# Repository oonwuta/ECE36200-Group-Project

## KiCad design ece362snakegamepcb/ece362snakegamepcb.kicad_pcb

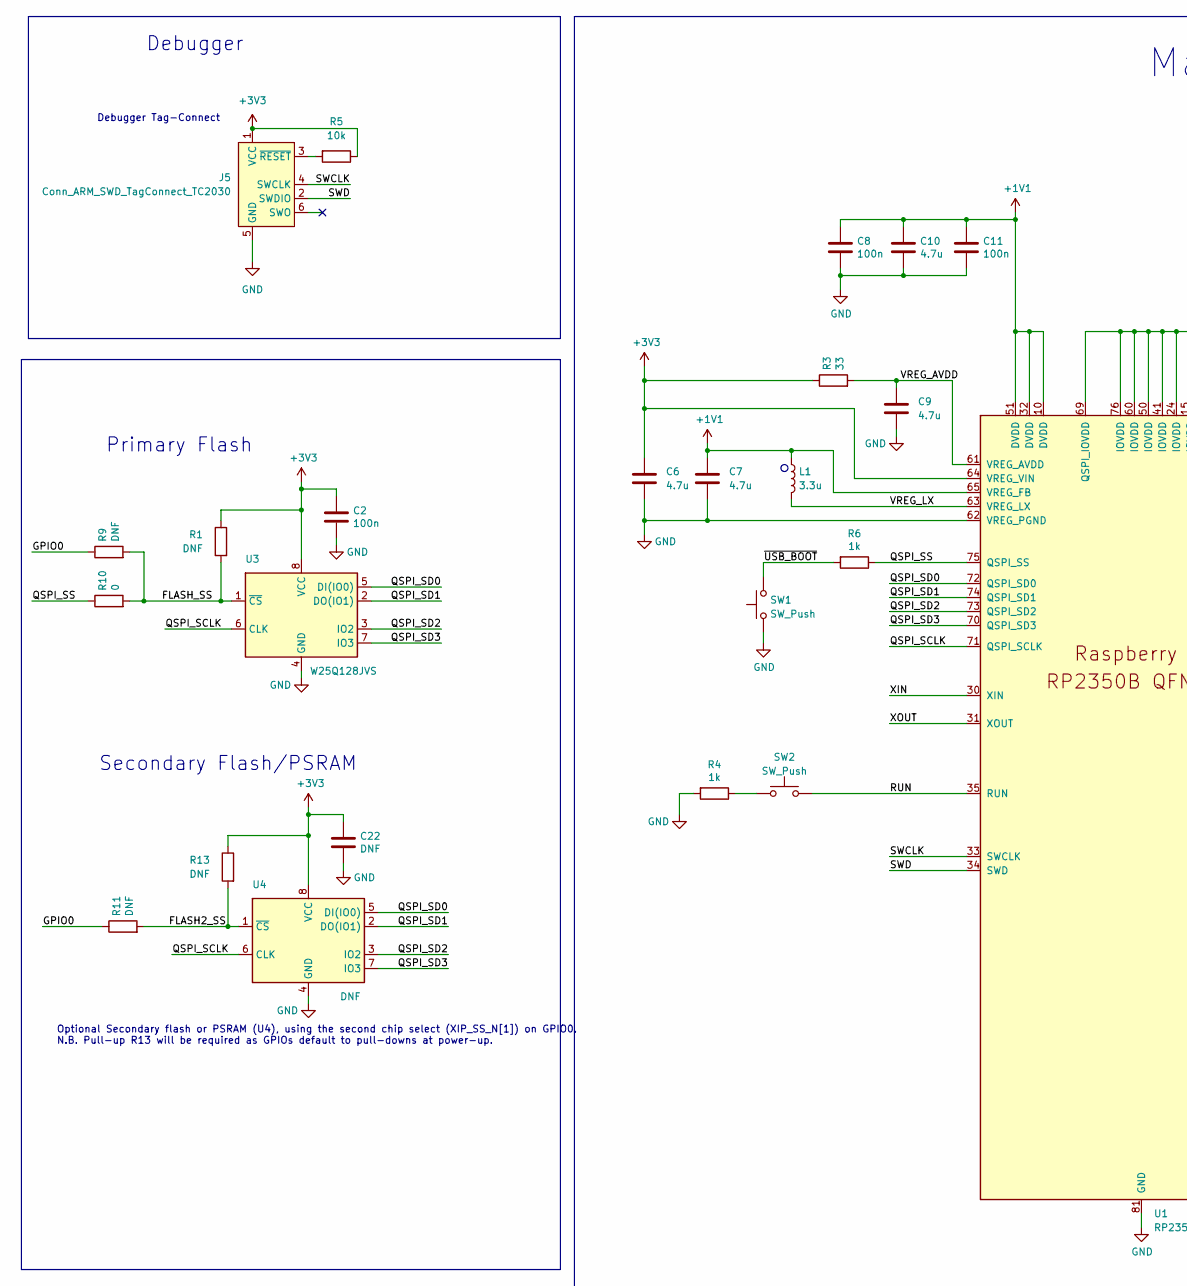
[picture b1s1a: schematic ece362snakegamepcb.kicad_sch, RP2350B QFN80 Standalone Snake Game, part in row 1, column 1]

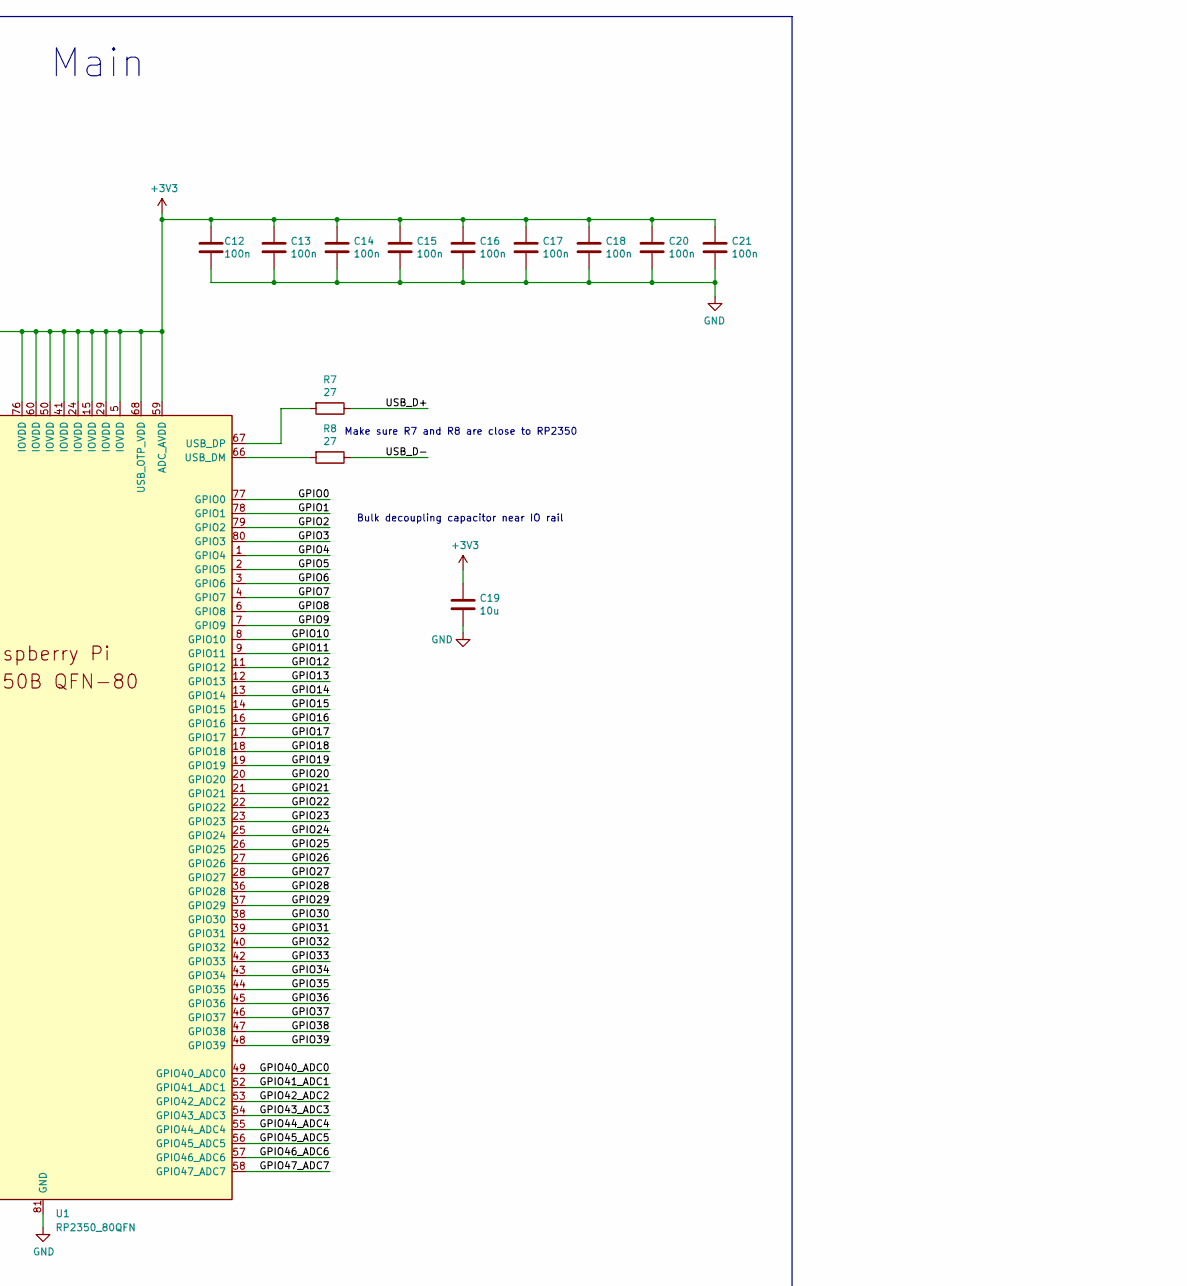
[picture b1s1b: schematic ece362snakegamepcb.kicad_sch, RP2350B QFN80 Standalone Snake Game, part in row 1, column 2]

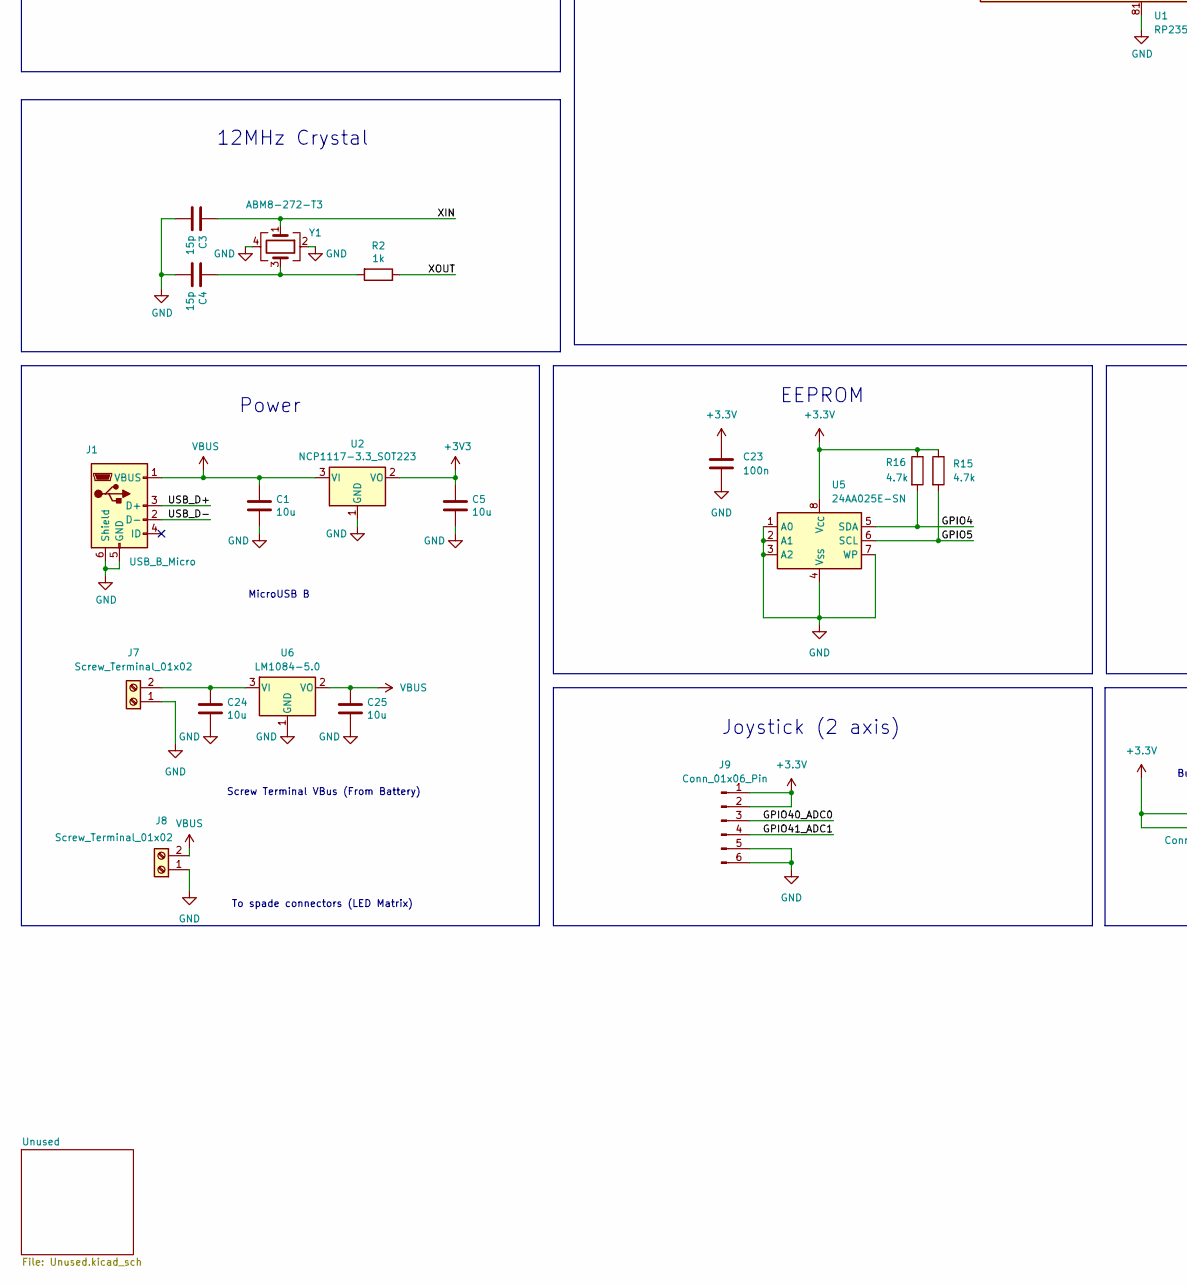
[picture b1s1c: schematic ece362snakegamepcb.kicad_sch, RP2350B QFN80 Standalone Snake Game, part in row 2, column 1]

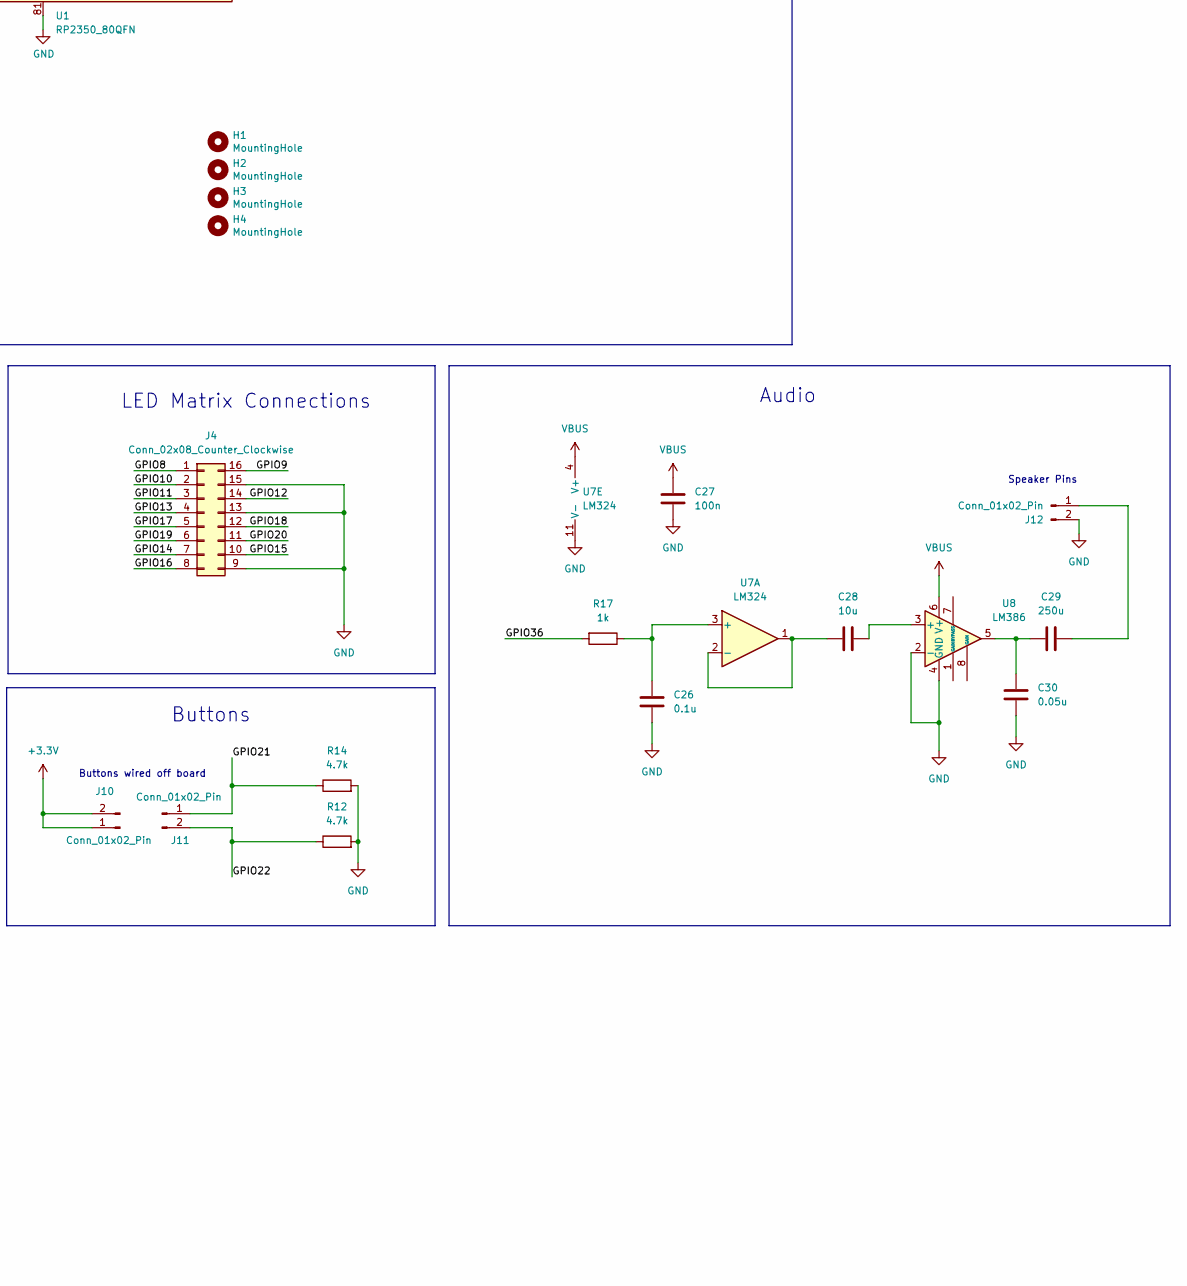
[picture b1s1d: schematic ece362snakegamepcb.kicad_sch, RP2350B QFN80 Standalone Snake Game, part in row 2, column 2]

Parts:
C1, C5, C19, C24, C25, C28: 10u; C_0805_2012Metric
C2, C8, C11, C12, C13, C14, C15, C16, C17, C18, C20, C21, C23, C27: 100n; C_0402_1005Metric
C3, C4: 15p; C_0402_1005Metric
C6, C7: 4.7u; C_0402_1005Metric_small_pads
C9, C10: 4.7u; C_0402_1005Metric
C22: DNF; C_0402_1005Metric
C26: 0.1u; C_0402_1005Metric
C29: 250u; C_0402_1005Metric
C30: 0.05u; C_0402_1005Metric
H1, H2, H3, H4: MountingHole; MountingHole_2.7mm_M2.5
J1: USB_B_Micro; USB_Micro-B_Amphenol_10103594-0001LF_Horizontal
J4: Conn_02x08_Counter_Clockwise; PinHeader_2x08_P2.54mm_Horizontal
J5: Conn_ARM_SWD_TagConnect_TC2030; Tag-Connect_TC2030-IDC-FP_2x03_P1.27mm_Vertical
J7, J8: Screw_Terminal_01x02; TerminalBlock_Phoenix_MPT-0,5-2-2.54_1x02_P2.54mm_Horizontal
J9: Conn_01x06_Pin; PinHeader_1x06_P2.54mm_Horizontal
J10, J11, J12: Conn_01x02_Pin; PinHeader_1x02_P2.54mm_Vertical
L1: 3.3u; L_pol_2016
R1, R9, R11, R13: DNF; R_0402_1005Metric
R2, R4, R6, R17: 1k; R_0402_1005Metric
R3: 33; R_0402_1005Metric
R5: 10k; R_0402_1005Metric
R7, R8: 27; R_0402_1005Metric
R10: 0; R_0402_1005Metric
R12, R14, R15, R16: 4.7k; R_0402_1005Metric
SW1, SW2: SW_Push; SW_Push_1P1T_NO_Vertical_Wuerth_434133025816
U1: RP2350_80QFN; RP2350-QFN-80-1EP_10x10_P0.4mm_EP3.4x3.4mm_ThermalVias
U2: NCP1117-3.3_SOT223; SOT-223-3_TabPin2
U3: W25Q128JVS; SOIC-8_5.23x5.23mm_P1.27mm
U4: DNF; SOIC-8_5.23x5.23mm_P1.27mm
U5: 24AA025E-SN; SOIC-8_3.9x4.9mm_P1.27mm
U6: LM1084-5.0; TO-220-3_Horizontal_TabDown
U7: LM324; SSOP-14_5.3x6.2mm_P0.65mm
U8: LM386; SOIC-8_3.9x4.9mm_P1.27mm
Y1: ABM8-272-T3; Crystal_SMD_3225-4Pin_3.2x2.5mm

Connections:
+1V1: C7.1, C8.1, C10.1, C11.1, L1.1, U1.10 (DVDD), U1.32 (DVDD), U1.51 (DVDD), U1.65 (VREG_FB)
+9V: C24.1, J7.2, U6.3 (VI)
/FLASH2_SS: R11.2, R13.2, U4.1 (~CS)
/FLASH_SS: R1.2, R9.2, R10.2, U3.1 (~CS)
/GPIO0: R9.1, R11.1, U1.77 (GPIO0)
/GPIO1: U1.78 (GPIO1)
/GPIO2: U1.79 (GPIO2)
/GPIO3: U1.80 (GPIO3)
/GPIO4: R16.2, U1.1 (GPIO4), U5.5 (SDA)
/GPIO5: R15.2, U1.2 (GPIO5), U5.6 (SCL)
/GPIO6: U1.3 (GPIO6)
/GPIO7: U1.4 (GPIO7)
/GPIO8: J4.1, U1.6 (GPIO8)
/GPIO9: J4.16, U1.7 (GPIO9)
/GPIO10: J4.2, U1.8 (GPIO10)
/GPIO11: J4.3, U1.9 (GPIO11)
/GPIO12: J4.14, U1.11 (GPIO12)
/GPIO13: J4.4, U1.12 (GPIO13)
/GPIO14: J4.7, U1.13 (GPIO14)
/GPIO15: J4.10, U1.14 (GPIO15)
/GPIO16: J4.8, U1.16 (GPIO16)
/GPIO17: J4.5, U1.17 (GPIO17)
/GPIO18: J4.12, U1.18 (GPIO18)
/GPIO19: J4.6, U1.19 (GPIO19)
/GPIO20: J4.11, U1.20 (GPIO20)
/GPIO21: J11.1, R14.1, U1.21 (GPIO21)
/GPIO22: J11.2, R12.1, U1.22 (GPIO22)
/GPIO23: U1.23 (GPIO23)
/GPIO24: U1.25 (GPIO24)
/GPIO25: U1.26 (GPIO25)
/GPIO26: U1.27 (GPIO26)
/GPIO27: U1.28 (GPIO27)
/GPIO28: U1.36 (GPIO28)
/GPIO29: U1.37 (GPIO29)
/GPIO30: U1.38 (GPIO30)
/GPIO31: U1.39 (GPIO31)
/GPIO32: U1.40 (GPIO32)
/GPIO33: U1.42 (GPIO33)
/GPIO34: U1.43 (GPIO34)
/GPIO35: U1.44 (GPIO35)
/GPIO36: R17.2, U1.45 (GPIO36)
/GPIO37: U1.46 (GPIO37)
/GPIO38: U1.47 (GPIO38)
/GPIO39: U1.48 (GPIO39)
/GPIO40_ADC0: J9.3, U1.49 (GPIO40_ADC0)
/GPIO41_ADC1: J9.4, U1.52 (GPIO41_ADC1)
/GPIO42_ADC2: U1.53 (GPIO42_ADC2)
/GPIO43_ADC3: U1.54 (GPIO43_ADC3)
/GPIO44_ADC4: U1.55 (GPIO44_ADC4)
/GPIO45_ADC5: U1.56 (GPIO45_ADC5)
/GPIO46_ADC6: U1.57 (GPIO46_ADC6)
/GPIO47_ADC7: U1.58 (GPIO47_ADC7)
/QSPI_SCLK: U1.71 (QSPI_SCLK), U3.6 (CLK), U4.6 (CLK)
/QSPI_SD0: U1.72 (QSPI_SD0), U3.5 (DI(IO0)), U4.5 (DI(IO0))
/QSPI_SD1: U1.74 (QSPI_SD1), U3.2 (DO(IO1)), U4.2 (DO(IO1))
/QSPI_SD2: U1.73 (QSPI_SD2), U3.3 (IO2), U4.3 (IO2)
/QSPI_SD3: U1.70 (QSPI_SD3), U3.7 (IO3), U4.7 (IO3)
/QSPI_SS: R6.1, R10.1, U1.75 (QSPI_SS)
/RUN: SW2.2, U1.35 (RUN)
/SWCLK: J5.4 (SWCLK), U1.33 (SWCLK)
/SWD: J5.2 (SWDIO), U1.34 (SWD)
/USB_D+: J1.3 (D+), R7.1
/USB_D-: J1.2 (D-), R8.1
/VREG_AVDD: C9.1, R3.2, U1.61 (VREG_AVDD)
/VREG_LX: L1.2, U1.63 (VREG_LX)
/XIN: C3.1, U1.30 (XIN), Y1.1
/XOUT: R2.1, U1.31 (XOUT)
/~USB_BOOT: R6.2, SW1.2
GND: C1.2, C2.2, C3.2, C4.2, C5.2, C6.2, C7.2, C8.2, C9.2, C10.2, C11.2, C12.2, C13.2, C14.2, C15.2, C16.2, C17.2, C18.2, C19.2, C20.2, C21.2, C22.2, C23.2, C24.2, C25.2, C26.2, C27.2, C30.2, J1.5 (GND), J1.6 (Shield), J4.9, J4.13, J4.15, J5.5 (GND), J7.1, J8.1, J9.5, J9.6, J12.2, R4.2, R12.2, R14.2, SW1.1, U1.62 (VREG_PGND), U1.81 (GND), U2.1 (GND), U3.4 (GND), U4.4 (GND), U5.1 (A0), U5.2 (A1), U5.3 (A2), U5.4 (V_{SS}), U5.7 (WP), U6.1 (GND), U7.11 (V-), U8.2 (-), U8.4 (GND), Y1.2, Y1.4
unnamed: C4.1, R2.2, Y1.3
unnamed: C29.2, C30.1, U8.5
unnamed: J5.3 (~RESET), R5.2
unnamed: C29.1, J12.1
unnamed: R4.1, SW2.1
unnamed: R8.2, U1.66 (USB_DM)
unnamed: R7.2, U1.67 (USB_DP)
unnamed: C26.1, R17.1, U7.3 (+)
unnamed: C28.2, U7.1, U7.2 (-)
unnamed: C28.1, U8.3 (+)
VBUS: C1.1, C25.1, C27.1, J1.1 (VBUS), J8.2, U2.3 (VI), U6.2 (VO), U7.4 (V+), U8.6 (V+)

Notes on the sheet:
Optional Secondary flash or PSRAM (U4), using the second chip select (XIP_SS_N[1]) on GPIO0. N.B. Pull-up R13 will be required as GPIOs default to pull-downs at power-up.
12MHz Crystal
Buttons wired off board
Audio
To spade connectors (LED Matrix)
LED Matrix Connections
Buttons
Speaker Pins
Primary Flash
Bulk decoupling capacitor near IO rail
Make sure R7 and R8 are close to RP2350
Screw Terminal VBus (From Battery)
Main
Secondary Flash/PSRAM
Joystick (2 axis)
Debugger Tag-Connect
Debugger
MicroUSB B
EEPROM
Power

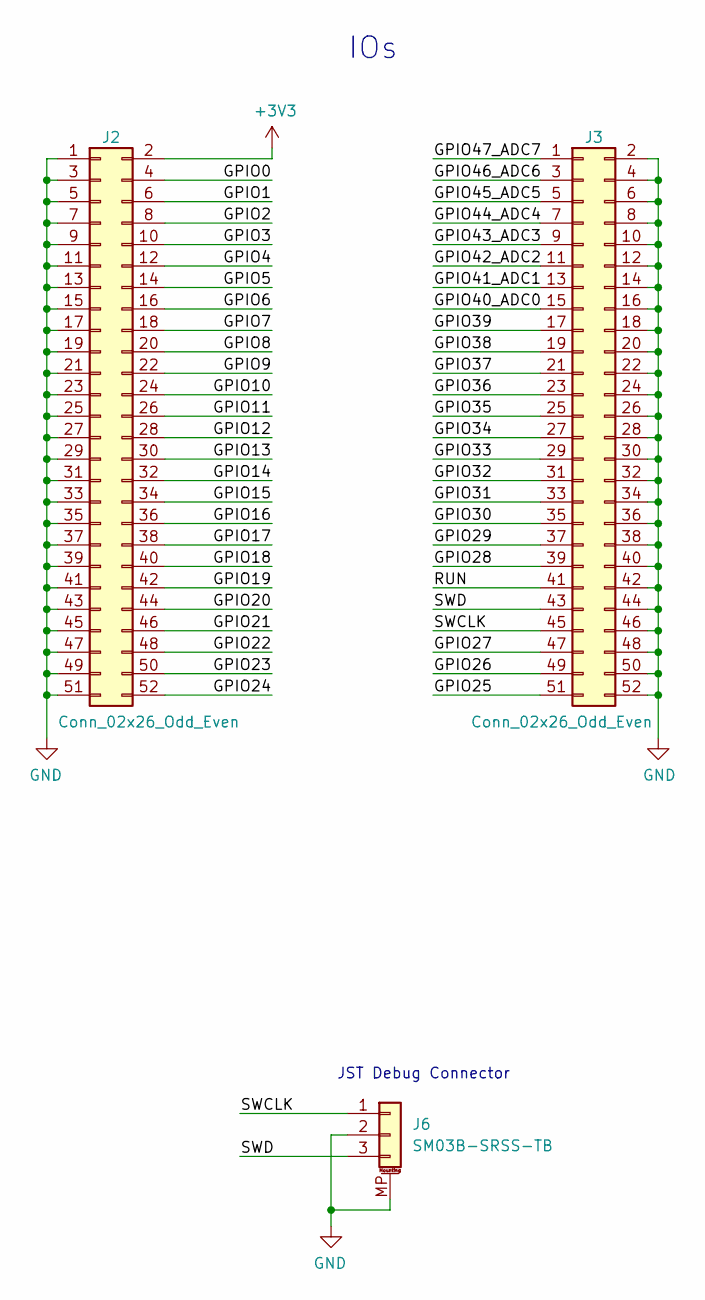
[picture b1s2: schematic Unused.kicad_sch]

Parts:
J2, J3: Conn_02x26_Odd_Even; PinHeader_2x26_P2.54mm_Vertical
J6: SM03B-SRSS-TB; JST_SH_SM03B-SRSS-TB_1x03-1MP_P1.00mm_Horizontal

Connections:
unnamed: J2.1, J2.3, J2.5, J2.7, J2.9, J2.11, J2.13, J2.15, J2.17, J2.19, J2.21, J2.23, J2.25, J2.27, J2.29, J2.31, J2.33, J2.35, J2.37, J2.39, J2.41, J2.43, J2.45, J2.47, J2.49, J2.51, J3.2, J3.4, J3.6, J3.8, J3.10, J3.12, J3.14, J3.16, J3.18, J3.20, J3.22, J3.24, J3.26, J3.28, J3.30, J3.32, J3.34, J3.36, J3.38, J3.40, J3.42, J3.44, J3.46, J3.48, J3.50, J3.52, J6.2, J6.MP (MountPin)
unnamed: J3.43, J6.3
unnamed: J3.45, J6.1

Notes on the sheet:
IOs
JST Debug Connector

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
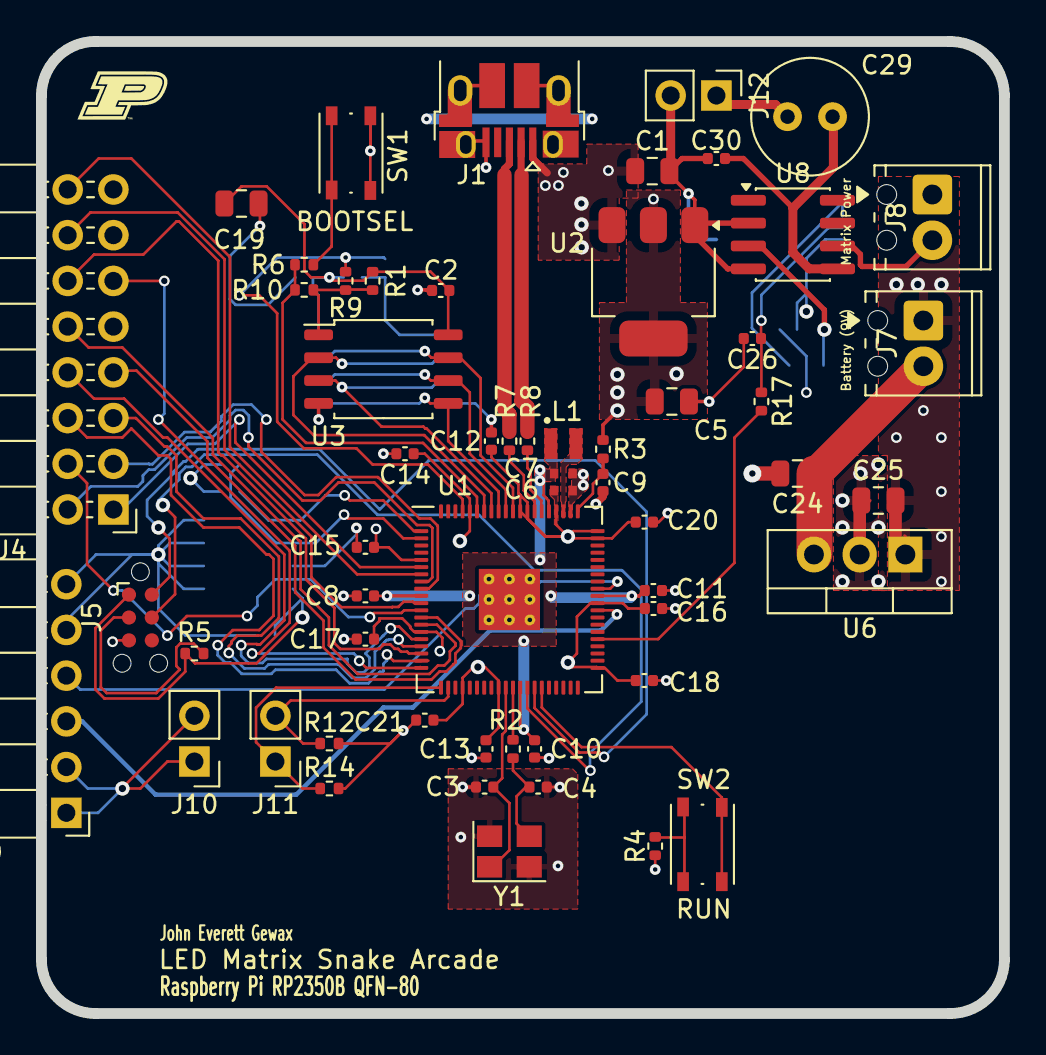
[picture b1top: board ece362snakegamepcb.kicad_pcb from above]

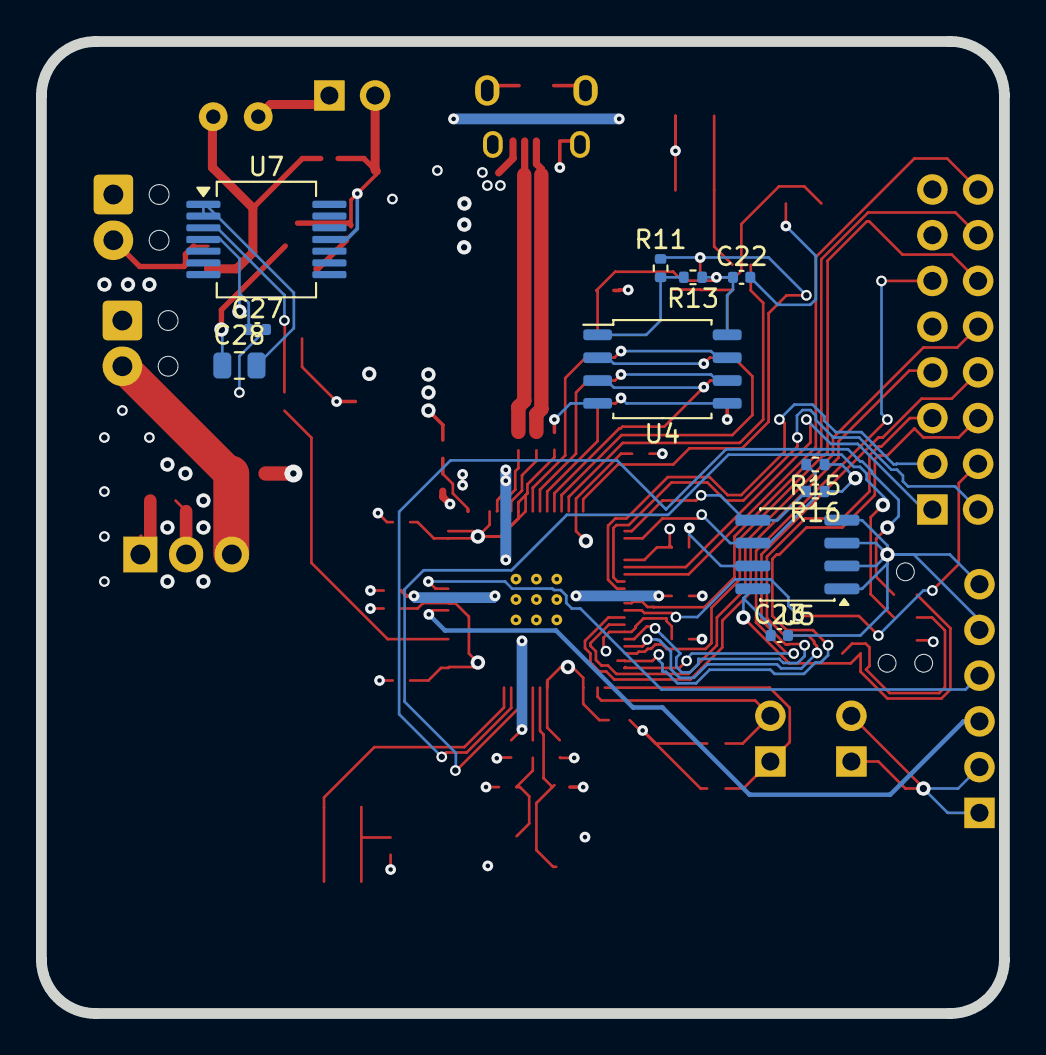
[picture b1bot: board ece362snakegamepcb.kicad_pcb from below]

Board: 4 copper layers, 53.5 x 54.0 mm, 68 parts (11 on the bottom side), 54 nets.

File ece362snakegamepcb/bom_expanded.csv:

Designator,Value,Footprint,LCSC
C1,10u,0805,CL21A106KAYNNNE
C19,10u,0805,CL21A106KAYNNNE
C24,10u,0805,CL21A106KAYNNNE
C25,10u,0805,CL21A106KAYNNNE
C28,10u,0805,CL21A106KAYNNNE
C5,10u,0805,CL21A106KAYNNNE
C10,4.7u,0402,CL05A475MP5NRNC
C6,4.7u,0402,CL05A475MP5NRNC
C7,4.7u,0402,CL05A475MP5NRNC
C9,4.7u,0402,CL05A475MP5NRNC
C11,100n,0402,CL05B104KO5NNNC
C12,100n,0402,CL05B104KO5NNNC
C13,100n,0402,CL05B104KO5NNNC
C14,100n,0402,CL05B104KO5NNNC
C15,100n,0402,CL05B104KO5NNNC
C16,100n,0402,CL05B104KO5NNNC
C17,100n,0402,CL05B104KO5NNNC
C18,100n,0402,CL05B104KO5NNNC
C2,100n,0402,CL05B104KO5NNNC
C20,100n,0402,CL05B104KO5NNNC
C21,100n,0402,CL05B104KO5NNNC
C23,100n,0402,CL05B104KO5NNNC
C27,100n,0402,CL05B104KO5NNNC
C8,100n,0402,CL05B104KO5NNNC
C22,DNF,0402,
R1,DNF,0402,
R11,DNF,0402,
R13,DNF,0402,
R9,DNF,0402,
C26,0.1u,0402,CL05B104KO5NNNC
C29,250u,C_Radial_D6.3mm_H5.0mm_P2.50mm,FVH010ADA221M0654
C3,15p,0402,0402CG150J500NT
C4,15p,0402,0402CG150J500NT
C30,0.05u,0402,GRM155R71C473KA01D
J1,USB_B_Micro,USB_Micro-B_Amphenol_10103594-0001LF_Horizontal,10103594-0001LF
J10,Conn_01x02_Pin,PinHeader_1x02_P2.54mm_Vertical,PZ2.54-1*2
J11,Conn_01x02_Pin,PinHeader_1x02_P2.54mm_Vertical,PZ2.54-1*2
J12,Conn_01x02_Pin,PinHeader_1x02_P2.54mm_Vertical,PZ2.54-1*2
J4,Conn_02x08_Counter_Clockwise,PinHeader_2x08_P2.54mm_Horizontal,2.54-2*8P弯简牛
J7,Screw_Terminal_01x02,"TerminalBlock_Phoenix_MPT-0,5-2-2.54_1x02_P2.54mm_Horizontal",1725656
J8,Screw_Terminal_01x02,"TerminalBlock_Phoenix_MPT-0,5-2-2.54_1x02_P2.54mm_Horizontal",1725656
J9,Conn_01x06_Pin,PinHeader_1x06_P2.54mm_Horizontal,2.54-1x6P直针
L1,3.3u,0806,AOTA-B201610S3R3-101-T
R10,0,0402,0402WGF0000TCE
R12,4.7k,0402,0402WGF4701TCE
R14,4.7k,0402,0402WGF4701TCE
R15,4.7k,0402,0402WGF4701TCE
R16,4.7k,0402,0402WGF4701TCE
R17,1k,0402,0402WGF1001TCE
R2,1k,0402,0402WGF1001TCE
R4,1k,0402,0402WGF1001TCE
R6,1k,0402,0402WGF1001TCE
R3,33,0402,0402WGF330JTCE
R5,10k,0402,0402WGF1002TCE
R7,27,0402,0402WGF270JTCE
R8,27,0402,0402WGF270JTCE
SW1,SW_Push,SW_Push_1P1T_NO_Vertical_Wuerth_434133025816,4.34133E+11
SW2,SW_Push,SW_Push_1P1T_NO_Vertical_Wuerth_434133025816,4.34133E+11
U1,RP2350_80QFN,RP2350-QFN-80-1EP_10x10_P0.4mm_EP3.4x3.4mm_ThermalVias,RP2350B
U2,NCP1117-3.3_SOT223,SOT-223-3_TabPin2,BL1117-33CX
U3,W25Q128JVS,SOIC-8_5.23x5.23mm_P1.27mm,W25Q128JVSIQ
U4,DNF,SOIC-8_5.23x5.23mm_P1.27mm,
U5,24AA025E-SN,SOIC-8_3.9x4.9mm_P1.27mm,24AA025E48-I/SN
U6,LM1084-5.0,TO-220-3_Horizontal_TabDown,LM1084IT-5.0/NOPB
U7,LM324,SSOP-14_5.3x6.2mm_P0.65mm,LM324
U8,LM386,SOIC-8_3.9x4.9mm_P1.27mm,LM386MX-1/NOPB
Y1,ABM8-272-T3,Crystal_SMD_3225-4Pin_3.2x2.5mm,ABM8-272-T3

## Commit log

2025-10-30 Skeleton for Project
2025-11-02 LED Display skeleton code
2025-11-03 Audio sample code from Lab 5 PWM
2025-11-05 Added menu with start to display with double buffering SPI
2025-11-05 So i guess I did a lot here, first made .h files for audio because it wouldn't compile when all that stuff was in audio.c, added music.c and music.h, havent tested it but it compiles w/o error and sh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
2025-11-05 Added kicad schematic start
    IOs section almost complete
2025-11-12 i2c to eeprom, not really sure if it works yet
2025-11-12 added display.h
2025-11-12 I'm trying to just get it to turn on... not finding much success
2025-11-12 merge
2025-11-15 Joystick and main function psuedocode
    Implemented x and y coordinates for the button, button input is not implemented due to questions on how it would work and questions on if the input would need to be debounced. Included comments about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
2025-11-19 Added ece362snakegamepcb project files and removed ece362course-project files
2025-11-19 i mean at least it lights up now
2025-11-20 Finished schematic and almost done with PCB layout. Removed autosave file and added several
2025-11-21 Finished pcb layout, but need to fix DRC erros
2025-11-21 done except some drc errors (mostly silkscreen):
2025-11-21 Fully completed. added gerbers, bom, placement
2025-11-22 Finished PCB for real this time
2025-11-27 Main Game Logic First Draft
    Un-tested main game code with some definite syntax errors.
2025-12-01 It works... might have had to restart to get it though
2025-12-01 fucked it up with the merge, that test didn't work anyway... hopefully this is right?
2025-12-01 fixed some dependencies
2025-12-01 Update to include refreshing and syntax errors
2025-12-01 Additional syntax changes
2025-12-03 Joystick Update
2025-12-03 WORK PLEASE
2025-12-03 Removed dma from joystick adc usage:
2025-12-03 removed start many adc
2025-12-03 return
2025-12-03 added print statements and init snake game changes
2025-12-03 audio
2025-12-04 fixed high score screen
2025-12-04 changes to main
2025-12-04 eeprom code, running into issues with test on highscore_load()
2025-12-04 Added game_board array, next up is the loop update logic
2025-12-04 notes..
2025-12-04 audio commit
2025-12-04 changed highscore code to add the 3 letter initial which i originally forgot. still same logic
2025-12-04 audio, added death sound for death, apple for apple, and volume control
2025-12-04 Game working sort of, need to fix death screen
2025-12-04 few changes for volume
2025-12-05 almost done
2025-12-05 fixed hs screen cursor bug
2025-12-05 Button Debouncing
2025-12-05 added music calls
2025-12-05 Debouncing 2
2025-12-05 updating audio and buttons
2025-12-05 Button debouncing with locking
